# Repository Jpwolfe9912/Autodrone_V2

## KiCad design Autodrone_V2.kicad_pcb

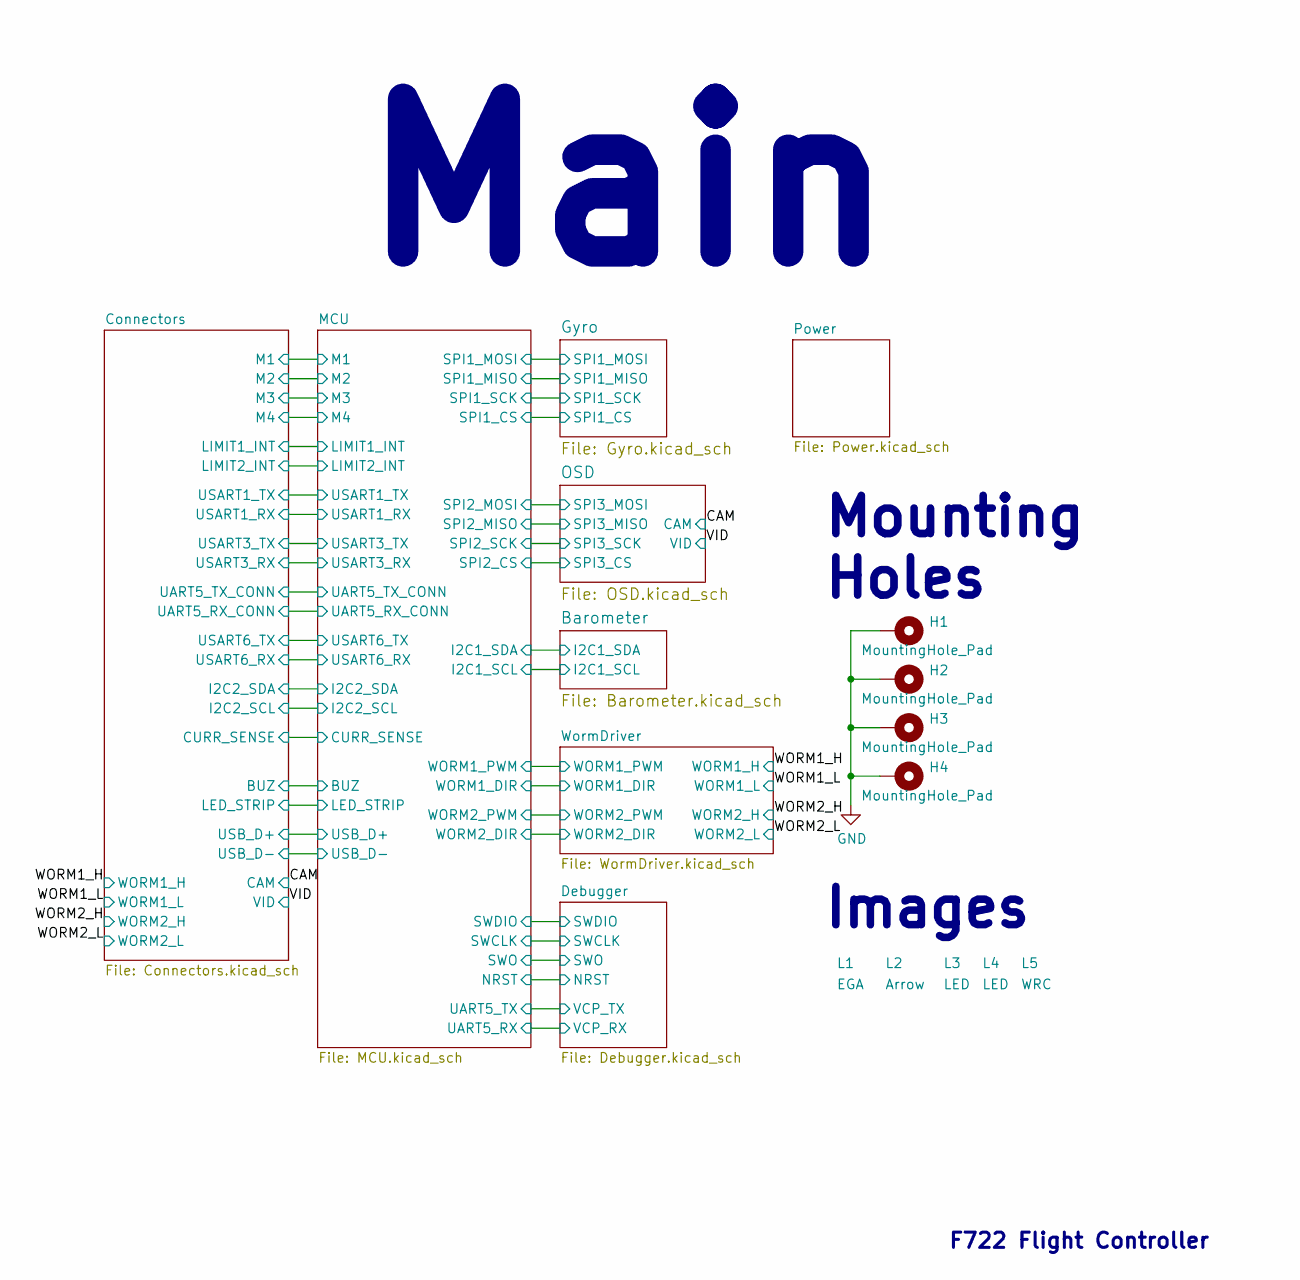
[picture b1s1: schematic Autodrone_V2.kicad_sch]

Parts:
H1, H2, H3, H4: MountingHole_Pad; MountingHole_6_4
L1: EGA
L2: Arrow
L3, L4: LED
L5: WRC; WRC2

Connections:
GND: H1.1, H2.1, H3.1, H4.1; also elsewhere on the board

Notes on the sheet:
Mounting Holes
Images
F722 Flight Controller
Main

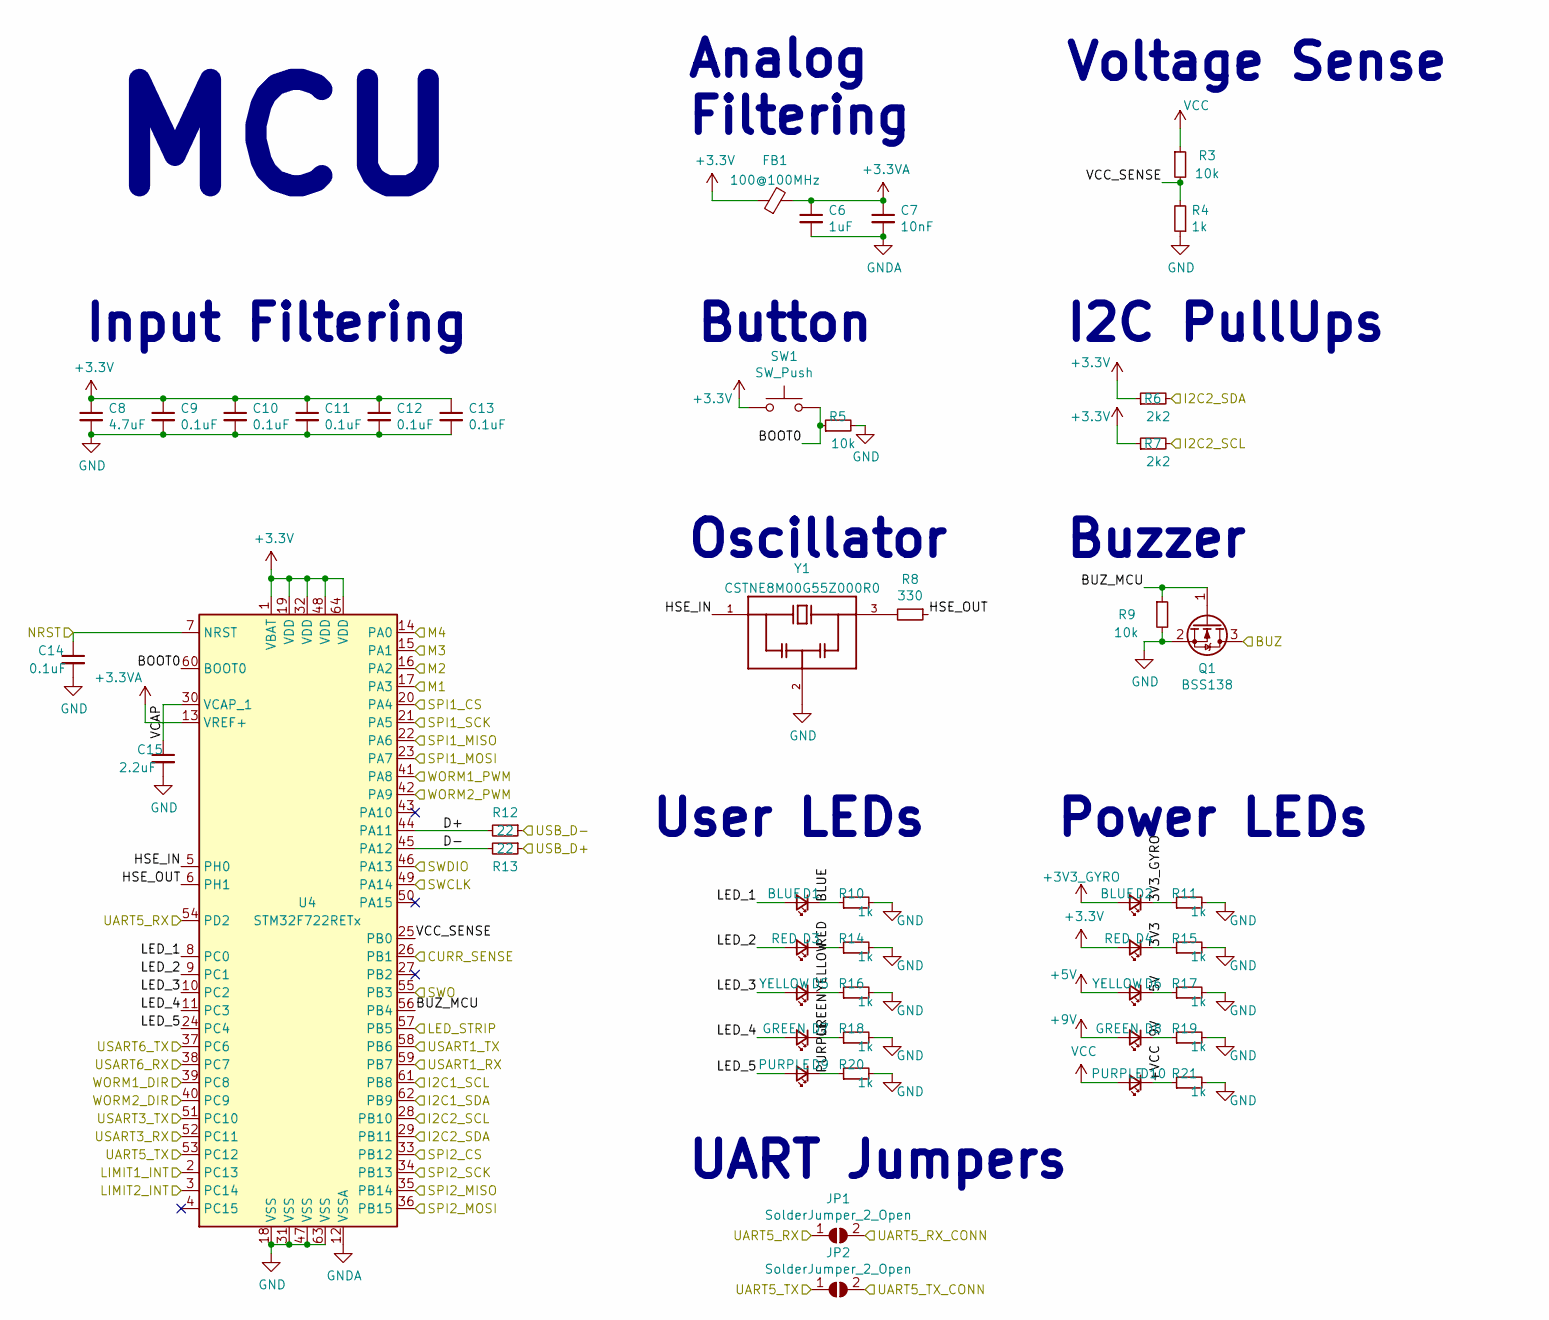
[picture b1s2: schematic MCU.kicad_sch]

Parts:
C6: 1uF; C_0402_1005Metric
C7: 10nF; C_0402_1005Metric
C8: 4.7uF; C_0402_1005Metric
C9, C10, C11, C12, C13, C14: 0.1uF; C_0402_1005Metric
C15: 2.2uF; C_0402_1005Metric
D1, D2: BLUE; LED_0603_1608Metric
D3, D4: RED; LED_0603_1608Metric
D5, D6: YELLOW; LED_0603_1608Metric
D7, D8: GREEN; LED_0603_1608Metric
D9, D10: PURPLE; LED_0603_1608Metric
FB1: 100@100MHz; L_0603_1608Metric
JP1, JP2: SolderJumper_2_Open; SolderJumper-2_P1.3mm_Open_TrianglePad1.0x1.5mm
Q1: BSS138; SOT-23
R3, R5, R9: 10k; R_0402_1005Metric
R4, R10, R11, R14, R15, R16, R17, R18, R19, R20, R21: 1k; R_0402_1005Metric
R6, R7: 2k2; R_0402_1005Metric
R8: 330; R_0402_1005Metric
R12, R13: 22; R_0402_1005Metric
SW1: SW_Push; SW_SPST_B3U-1000P
U4: STM32F722RETx; LQFP-64_10x10mm_P0.5mm
Y1: CSTNE8M00G55Z000R0; OSC_CSTNE8M00G55Z000R0; PARTREV JGC42-8858A

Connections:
+3.3VA: C6.1, C7.1, FB1.2, U4.13 (VREF+)
+3V3_GYRO: D2.2 (A); also elsewhere on the board
+5V: D6.2 (A); also elsewhere on the board
+9V: D8.2 (A); also elsewhere on the board
/Barometer/I2C1_SCL: U4.61 (PB8); also elsewhere on the board
/Barometer/I2C1_SDA: U4.62 (PB9); also elsewhere on the board
/Connectors/BUZ: Q1.3 (D); also elsewhere on the board
/Connectors/CURR_SENSE: U4.26 (PB1); also elsewhere on the board
/Connectors/I2C2_SCL: R7.2, U4.28 (PB10); also elsewhere on the board
/Connectors/I2C2_SDA: R6.2, U4.29 (PB11); also elsewhere on the board
/Connectors/LED_STRIP: U4.57 (PB5); also elsewhere on the board
/Connectors/LIMIT1_INT: U4.2 (PC13); also elsewhere on the board
/Connectors/LIMIT2_INT: U4.3 (PC14); also elsewhere on the board
/Connectors/M1: U4.17 (PA3); also elsewhere on the board
/Connectors/M2: U4.16 (PA2); also elsewhere on the board
/Connectors/M3: U4.15 (PA1); also elsewhere on the board
/Connectors/M4: U4.14 (PA0); also elsewhere on the board
/Connectors/UART5_RX_CONN: JP1.2 (B); also elsewhere on the board
/Connectors/UART5_TX_CONN: JP2.2 (B); also elsewhere on the board
/Connectors/USART1_RX: U4.59 (PB7); also elsewhere on the board
/Connectors/USART1_TX: U4.58 (PB6); also elsewhere on the board
/Connectors/USART3_RX: U4.52 (PC11); also elsewhere on the board
/Connectors/USART3_TX: U4.51 (PC10); also elsewhere on the board
/Connectors/USART6_RX: U4.38 (PC7); also elsewhere on the board
/Connectors/USART6_TX: U4.37 (PC6); also elsewhere on the board
/Connectors/USB_D+: R13.1; also elsewhere on the board
/Connectors/USB_D-: R12.1; also elsewhere on the board
/Debugger/NRST: C14.1, U4.7 (NRST); also elsewhere on the board
/Debugger/SWCLK: U4.49 (PA14); also elsewhere on the board
/Debugger/SWDIO: U4.46 (PA13); also elsewhere on the board
/Debugger/SWO: U4.55 (PB3); also elsewhere on the board
/Debugger/VCP_RX: JP1.1 (A), U4.54 (PD2); also elsewhere on the board
/Debugger/VCP_TX: JP2.1 (A), U4.53 (PC12); also elsewhere on the board
/Gyro/SPI1_CS: U4.20 (PA4); also elsewhere on the board
/Gyro/SPI1_MISO: U4.22 (PA6); also elsewhere on the board
/Gyro/SPI1_MOSI: U4.23 (PA7); also elsewhere on the board
/Gyro/SPI1_SCK: U4.21 (PA5); also elsewhere on the board
/MCU/3V3: D4.1 (K), R15.1
/MCU/3V3_GYRO: D2.1 (K), R11.1
/MCU/5V: D6.1 (K), R17.1
/MCU/9V: D8.1 (K), R19.1
/MCU/+VCC: D10.1 (K), R21.1
/MCU/BLUE: D1.1 (K), R10.1
/MCU/BOOT0: R5.1, SW1.2, U4.60 (BOOT0)
/MCU/BUZ_MCU: Q1.1 (G), R9.1, U4.56 (PB4)
/MCU/D+: R12.2, U4.44 (PA11)
/MCU/D-: R13.2, U4.45 (PA12)
/MCU/GREEN: D7.1 (K), R18.1
/MCU/HSE_IN: U4.5 (PH0), Y1.1
/MCU/HSE_OUT: R8.1, U4.6 (PH1)
/MCU/LED_1: D1.2 (A), U4.8 (PC0)
/MCU/LED_2: D3.2 (A), U4.9 (PC1)
/MCU/LED_3: D5.2 (A), U4.10 (PC2)
/MCU/LED_4: D7.2 (A), U4.11 (PC3)
/MCU/LED_5: D9.2 (A), U4.24 (PC4)
/MCU/PURPLE: D9.1 (K), R20.1
/MCU/RED: D3.1 (K), R14.1
/MCU/SPI2_CS: U4.33 (PB12); also elsewhere on the board
/MCU/SPI2_MISO: U4.35 (PB14); also elsewhere on the board
/MCU/SPI2_MOSI: U4.36 (PB15); also elsewhere on the board
/MCU/SPI2_SCK: U4.34 (PB13); also elsewhere on the board
/MCU/VCAP: C15.1, U4.30 (VCAP_1)
/MCU/VCC_SENSE: R3.2, R4.2, U4.25 (PB0)
/MCU/WORM1_DIR: U4.39 (PC8); also elsewhere on the board
/MCU/WORM1_PWM: U4.41 (PA8); also elsewhere on the board
/MCU/WORM2_DIR: U4.40 (PC9); also elsewhere on the board
/MCU/WORM2_PWM: U4.42 (PA9); also elsewhere on the board
/MCU/YELLOW: D5.1 (K), R16.1
GND: C8.2, C9.2, C10.2, C11.2, C12.2, C13.2, C14.2, C15.2, Q1.2 (S), R4.1, R5.2, R9.2, R10.2, R11.2, R14.2, R15.2, R16.2, R17.2, R18.2, R19.2, R20.2, R21.2, U4.18 (VSS), U4.31 (VSS), U4.47 (VSS), U4.63 (VSS), Y1.2; also elsewhere on the board
GNDA: C6.2, C7.2, U4.12 (VSSA)
unnamed: R8.2, Y1.3
VCC: D10.2 (A), R3.1; also elsewhere on the board

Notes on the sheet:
MCU
User LEDs
Buzzer
UART Jumpers
Analog Filtering
Input Filtering
Oscillator
I2C PullUps
Button
Voltage Sense
Power LEDs

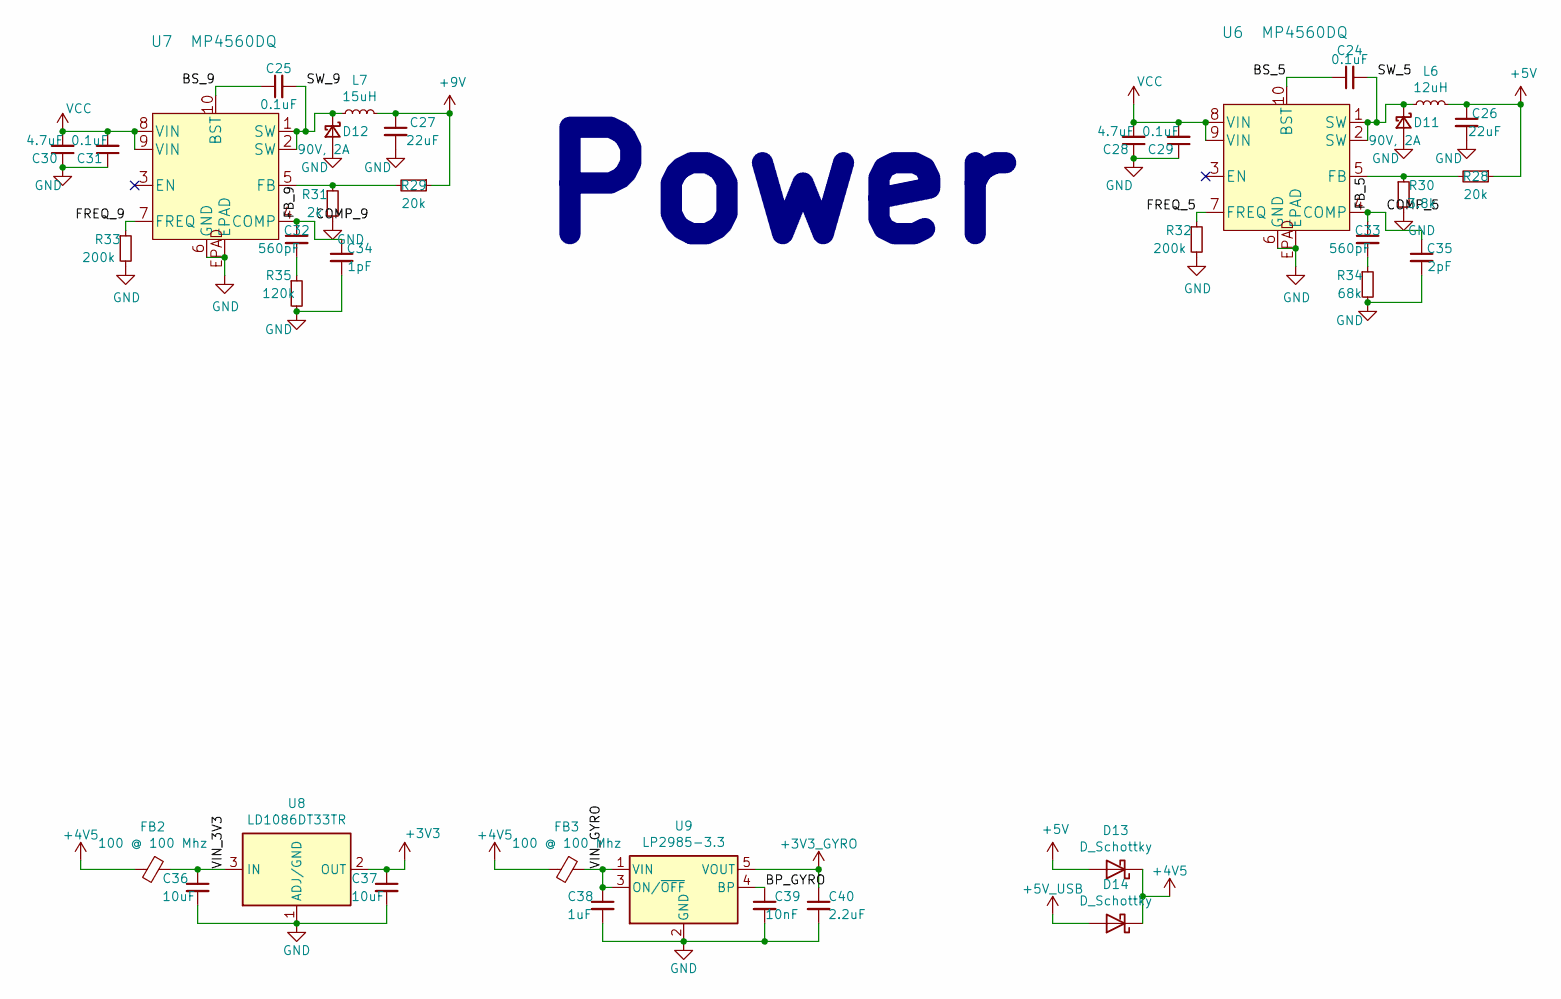
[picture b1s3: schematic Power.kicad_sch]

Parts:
C24, C25, C29, C31: 0.1uF; C_0402_1005Metric
C26, C27: 22uF; C_0805_2012Metric
C28, C30: 4.7uF; C_0402_1005Metric
C32, C33: 560pF; C_0402_1005Metric
C34: 1pF; C_0402_1005Metric
C35: 2pF; C_0402_1005Metric
C36, C37: 10uF; C_0402_1005Metric
C38: 1uF; C_0402_1005Metric
C39: 10nF; C_0402_1005Metric
C40: 2.2uF; C_0402_1005Metric
D11, D12: 90V, 2A; D_SOD-123F
D13, D14: D_Schottky; D_SOD-123F
FB2, FB3: 100 @ 100 Mhz; L_0603_1608Metric
L6: 12uH; L_Bourns_SRN3015
L7: 15uH; L_Bourns_SRN3015
R28, R29: 20k; R_0402_1005Metric
R30: 3.8k; R_0402_1005Metric
R31: 2k; R_0402_1005Metric
R32, R33: 200k; R_0402_1005Metric
R34: 68k; R_0402_1005Metric
R35: 120k; R_0402_1005Metric
U6, U7: MP4560DQ
U8: LD1086DT33TR; TO-252-2
U9: LP2985-3.3; SOT-23-5

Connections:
+3V3_GYRO: C40.1, U9.5 (VOUT); also elsewhere on the board
+4V5: D13.1 (K), D14.1 (K), FB2.2, FB3.2; also elsewhere on the board
+5V: C26.1, D13.2 (A), L6.2, R28.1; also elsewhere on the board
+5V_USB: D14.2 (A); also elsewhere on the board
+9V: C27.1, L7.2, R29.1; also elsewhere on the board
/Power/BP_GYRO: C39.1, U9.4 (BP)
/Power/BS_5: C24.1, U6.10 (BST)
/Power/BS_9: C25.1, U7.10 (BST)
/Power/COMP_5: C33.1, C35.1, U6.4 (COMP)
/Power/COMP_9: C32.1, C34.1, U7.4 (COMP)
/Power/FB_5: R28.2, R30.1, U6.5 (FB)
/Power/FB_9: R29.2, R31.1, U7.5 (FB)
/Power/FREQ_5: R32.1, U6.7 (FREQ)
/Power/FREQ_9: R33.1, U7.7 (FREQ)
/Power/SW_5: C24.2, D11.1 (K), L6.1, U6.1 (SW), U6.2 (SW)
/Power/SW_9: C25.2, D12.1 (K), L7.1, U7.1 (SW), U7.2 (SW)
/Power/VIN_3V3: C36.1, FB2.1, U8.3 (IN)
/Power/VIN_GYRO: C38.1, FB3.1, U9.1 (VIN), U9.3 (ON/~OFF)
GND: C26.2, C27.2, C28.1, C29.1, C30.1, C31.1, C34.2, C35.2, C36.2, C37.2, C38.2, C39.2, C40.2, D11.2 (A), D12.2 (A), R30.2, R31.2, R32.2, R33.2, R34.2, R35.2, U6.6 (GND), U6.EPAD, U7.6 (GND), U7.EPAD, U8.1 (ADJ/GND), U9.2 (GND); also elsewhere on the board
unnamed: C32.2, R35.1
unnamed: C33.2, R34.1
VCC: C28.2, C29.2, C30.2, C31.2, U6.8 (VIN), U6.9 (VIN), U7.8 (VIN), U7.9 (VIN); also elsewhere on the board

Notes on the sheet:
Power

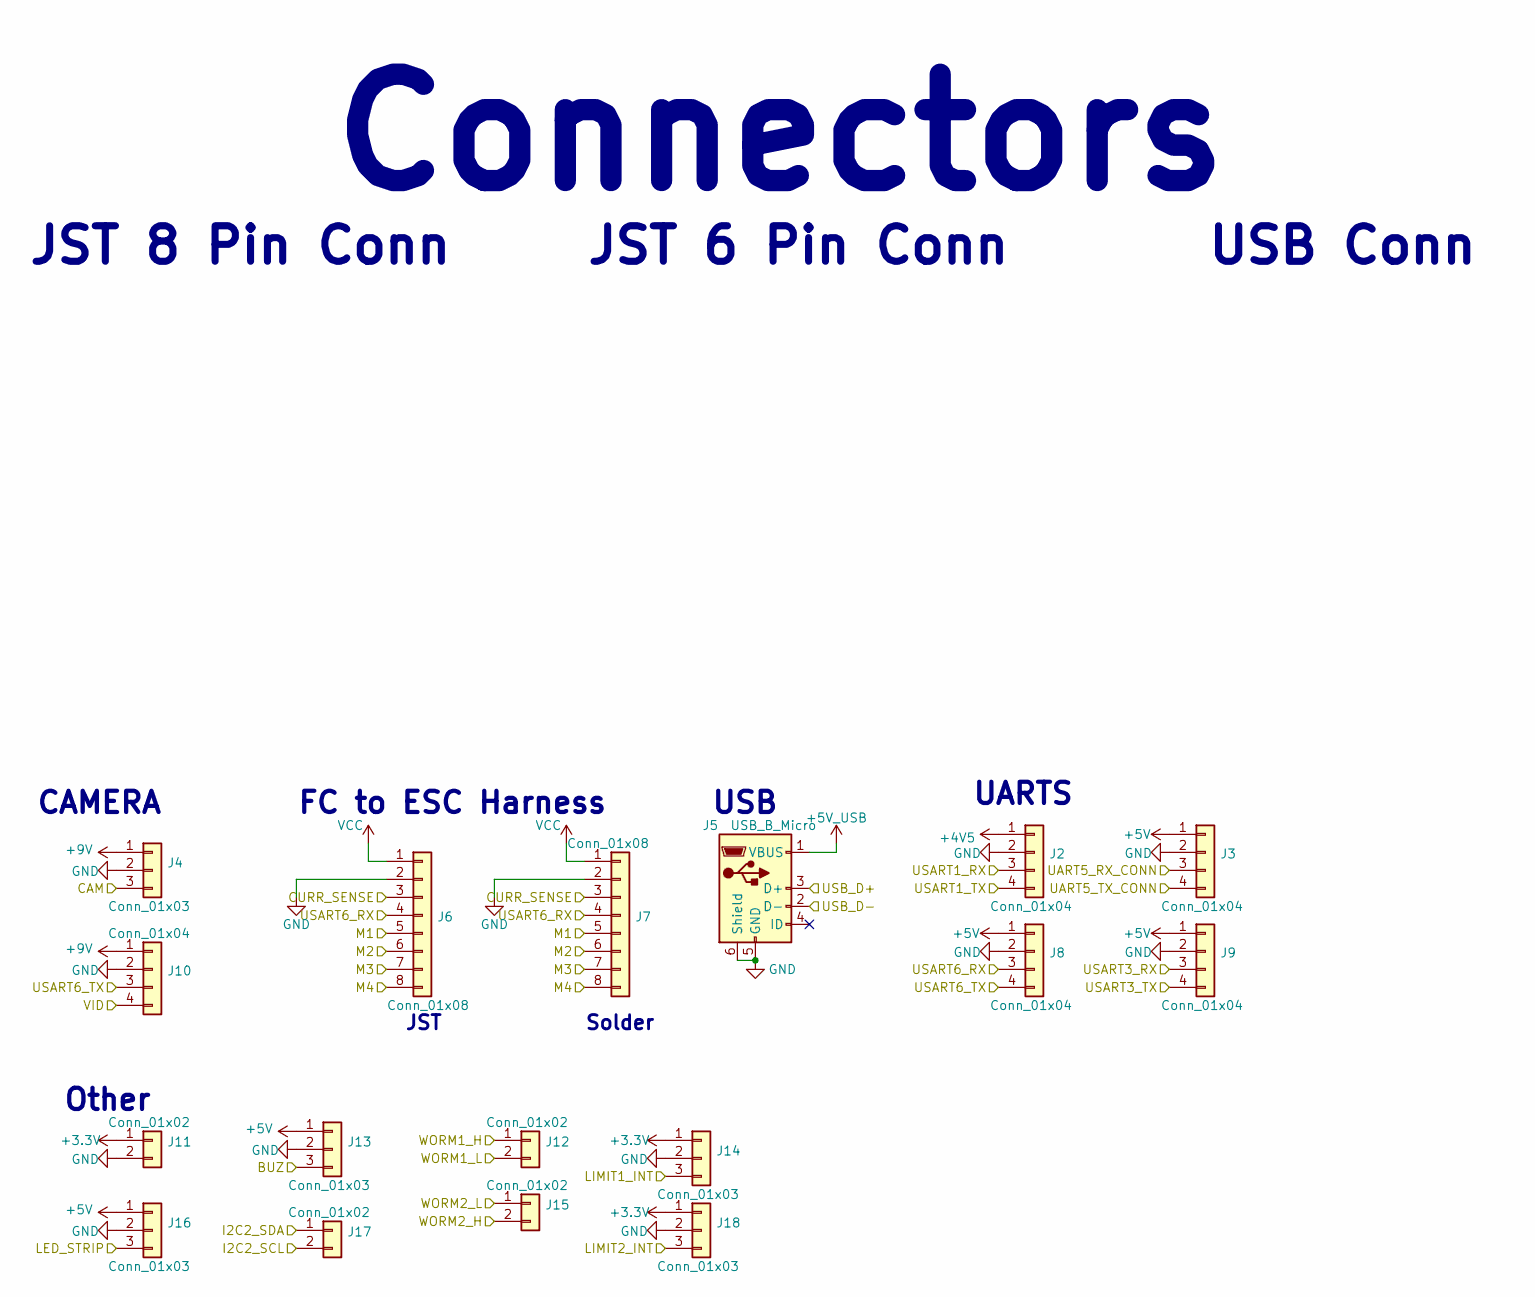
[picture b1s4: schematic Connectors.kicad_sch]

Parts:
J2, J3, J8, J9, J10: Conn_01x04; Conn_1x4
J4, J13, J14, J16, J18: Conn_01x03; Conn_1x3
J5: USB_B_Micro; USB_Micro-B_Amphenol_10103594-0001LF_Horizontal
J6: Conn_01x08; JST_SH_SM08B-SRSS-TB_1x08-1MP_P1.00mm_Horizontal
J7: Conn_01x08; Conn_8Edge
J11, J17: Conn_01x02; Conn_1x2
J12: Conn_01x02; Conn_Motor1
J15: Conn_01x02; Conn_Motor2

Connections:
+4V5: J2.1; also elsewhere on the board
+5V: J3.1, J8.1, J9.1, J13.1, J16.1; also elsewhere on the board
+5V_USB: J5.1 (VBUS); also elsewhere on the board
+9V: J4.1, J10.1; also elsewhere on the board
/CAM: J4.3; also elsewhere on the board
/Connectors/BUZ: J13.3; also elsewhere on the board
/Connectors/CURR_SENSE: J6.3, J7.3; also elsewhere on the board
/Connectors/I2C2_SCL: J17.2; also elsewhere on the board
/Connectors/I2C2_SDA: J17.1; also elsewhere on the board
/Connectors/LED_STRIP: J16.3; also elsewhere on the board
/Connectors/LIMIT1_INT: J14.3; also elsewhere on the board
/Connectors/LIMIT2_INT: J18.3; also elsewhere on the board
/Connectors/M1: J6.5, J7.5; also elsewhere on the board
/Connectors/M2: J6.6, J7.6; also elsewhere on the board
/Connectors/M3: J6.7, J7.7; also elsewhere on the board
/Connectors/M4: J6.8, J7.8; also elsewhere on the board
/Connectors/UART5_RX_CONN: J3.3; also elsewhere on the board
/Connectors/UART5_TX_CONN: J3.4; also elsewhere on the board
/Connectors/USART1_RX: J2.3; also elsewhere on the board
/Connectors/USART1_TX: J2.4; also elsewhere on the board
/Connectors/USART3_RX: J9.3; also elsewhere on the board
/Connectors/USART3_TX: J9.4; also elsewhere on the board
/Connectors/USART6_RX: J6.4, J7.4, J8.3; also elsewhere on the board
/Connectors/USART6_TX: J8.4, J10.3; also elsewhere on the board
/Connectors/USB_D+: J5.3 (D+); also elsewhere on the board
/Connectors/USB_D-: J5.2 (D-); also elsewhere on the board
/VID: J10.4; also elsewhere on the board
/WORM1_H: J12.1; also elsewhere on the board
/WORM1_L: J12.2; also elsewhere on the board
/WORM2_H: J15.2; also elsewhere on the board
/WORM2_L: J15.1; also elsewhere on the board
GND: J2.2, J3.2, J4.2, J5.5 (GND), J5.6 (Shield), J6.2, J7.2, J8.2, J9.2, J10.2, J11.2, J13.2, J14.2, J16.2, J18.2; also elsewhere on the board
VCC: J6.1, J7.1; also elsewhere on the board

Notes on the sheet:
USB
Solder
JST 8 Pin Conn
JST
CAMERA
UARTS
Connectors
FC to ESC Harness
Other
JST 6 Pin Conn
USB Conn

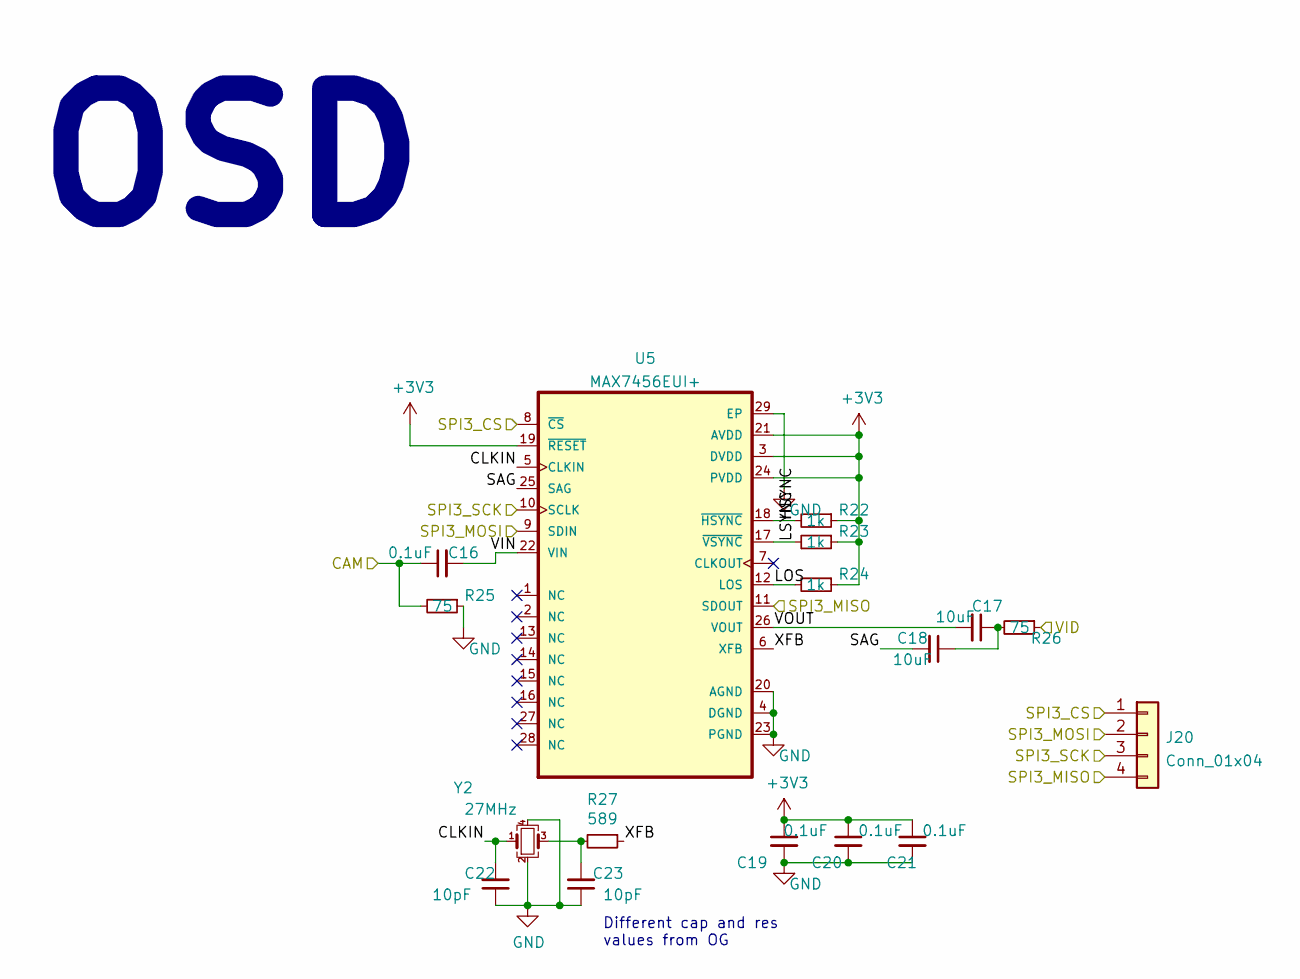
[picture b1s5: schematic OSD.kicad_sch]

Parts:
C16, C19, C20, C21: 0.1uF; C_0402_1005Metric
C17, C18: 10uF; C_0402_1005Metric
C22, C23: 10pF; C_0402_1005Metric
J20: Conn_01x04; SPI_Probe
R22, R23, R24: 1k; R_0402_1005Metric
R25, R26: 75; R_0402_1005Metric
R27: 589; R_0402_1005Metric
U5: MAX7456EUI+; MAX7456
Y2: 27MHz; Oscillator_SMD_Abracon_ASE-4Pin_3.2x2.5mm

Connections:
/CAM: C16.1, R25.2; also elsewhere on the board
/MCU/SPI2_CS: J20.1, U5.8 (~CS); also elsewhere on the board
/MCU/SPI2_MISO: J20.4, U5.11 (SDOUT); also elsewhere on the board
/MCU/SPI2_MOSI: J20.2, U5.9 (SDIN); also elsewhere on the board
/MCU/SPI2_SCK: J20.3, U5.10 (SCLK); also elsewhere on the board
/OSD/CLKIN: C22.2, U5.5 (CLKIN), Y2.1
/OSD/HSYNC: R22.2, U5.18 (~HSYNC)
/OSD/LOS: R24.2, U5.12 (LOS)
/OSD/LSYNC: R23.2, U5.17 (~VSYNC)
/OSD/SAG: C18.2, U5.25 (SAG)
/OSD/VIN: C16.2, U5.22 (VIN)
/OSD/VOUT: C17.2, U5.26 (VOUT)
/OSD/XFB: R27.1, U5.6 (XFB)
/VID: R26.1; also elsewhere on the board
GND: C19.2, C20.2, C21.2, C22.1, C23.1, R25.1, U5.4 (DGND), U5.20 (AGND), U5.23 (PGND), U5.29 (EP), Y2.2, Y2.4; also elsewhere on the board
unnamed: C17.1, C18.1, R26.2
unnamed: C23.2, R27.2, Y2.3

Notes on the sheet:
Different cap and res values from OG
OSD

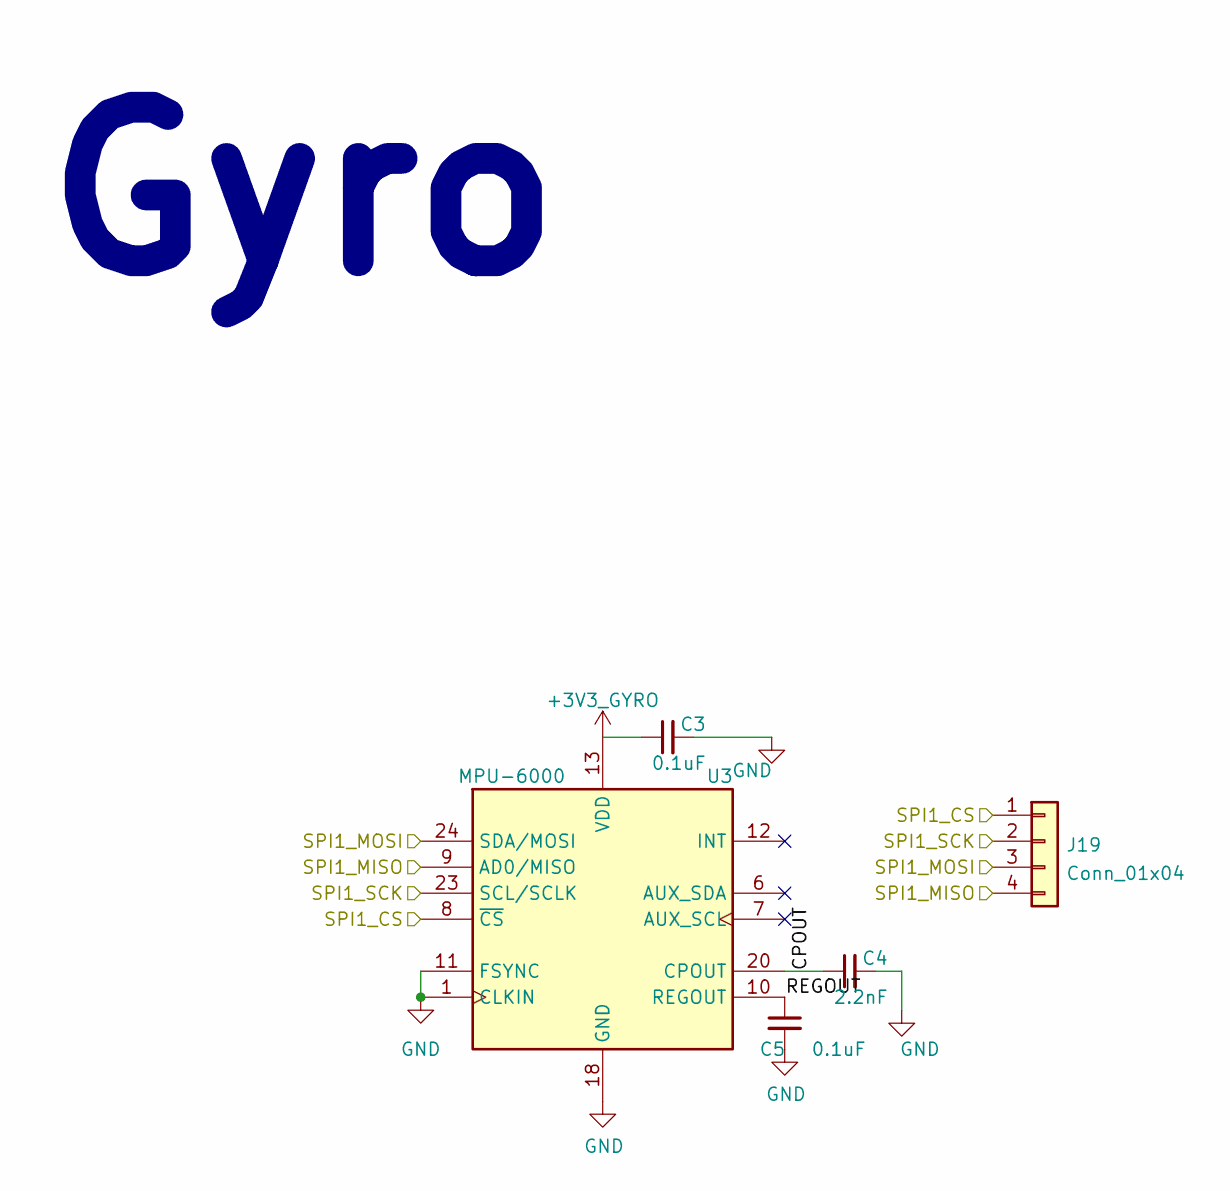
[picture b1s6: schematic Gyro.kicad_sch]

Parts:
C3, C5: 0.1uF; C_0402_1005Metric
C4: 2.2nF; C_0402_1005Metric
J19: Conn_01x04; SPI_Probe
U3: MPU-6000; InvenSense_QFN-24_4x4mm_P0.5mm

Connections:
+3V3_GYRO: C3.1, U3.13 (VDD); also elsewhere on the board
/Gyro/CPOUT: C4.1, U3.20 (CPOUT)
/Gyro/REGOUT: C5.1, U3.10 (REGOUT)
/Gyro/SPI1_CS: J19.1, U3.8 (~CS); also elsewhere on the board
/Gyro/SPI1_MISO: J19.4, U3.9 (AD0/MISO); also elsewhere on the board
/Gyro/SPI1_MOSI: J19.3, U3.24 (SDA/MOSI); also elsewhere on the board
/Gyro/SPI1_SCK: J19.2, U3.23 (SCL/SCLK); also elsewhere on the board
GND: C3.2, C4.2, C5.2, U3.1 (CLKIN), U3.11 (FSYNC), U3.18 (GND); also elsewhere on the board

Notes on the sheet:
Gyro

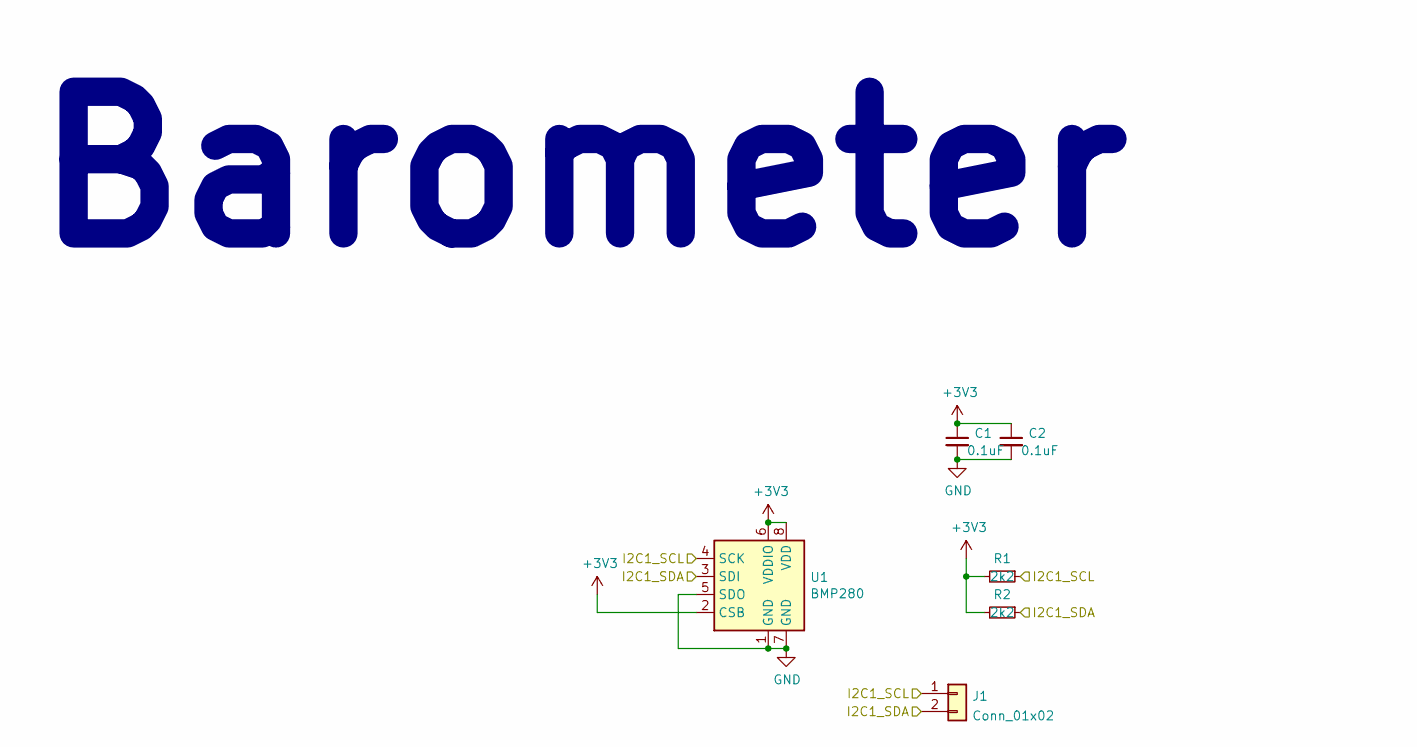
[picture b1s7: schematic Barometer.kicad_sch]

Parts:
C1, C2: 0.1uF; C_0402_1005Metric
J1: Conn_01x02; I2C_Probe
R1, R2: 2k2; R_0402_1005Metric
U1: BMP280; Bosch_LGA-8_2x2.5mm_P0.65mm_ClockwisePinNumbering

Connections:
/Barometer/I2C1_SCL: J1.1, R1.1, U1.4 (SCK); also elsewhere on the board
/Barometer/I2C1_SDA: J1.2, R2.1, U1.3 (SDI); also elsewhere on the board
GND: C1.2, C2.2, U1.1 (GND), U1.5 (SDO), U1.7 (GND); also elsewhere on the board

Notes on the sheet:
Barometer

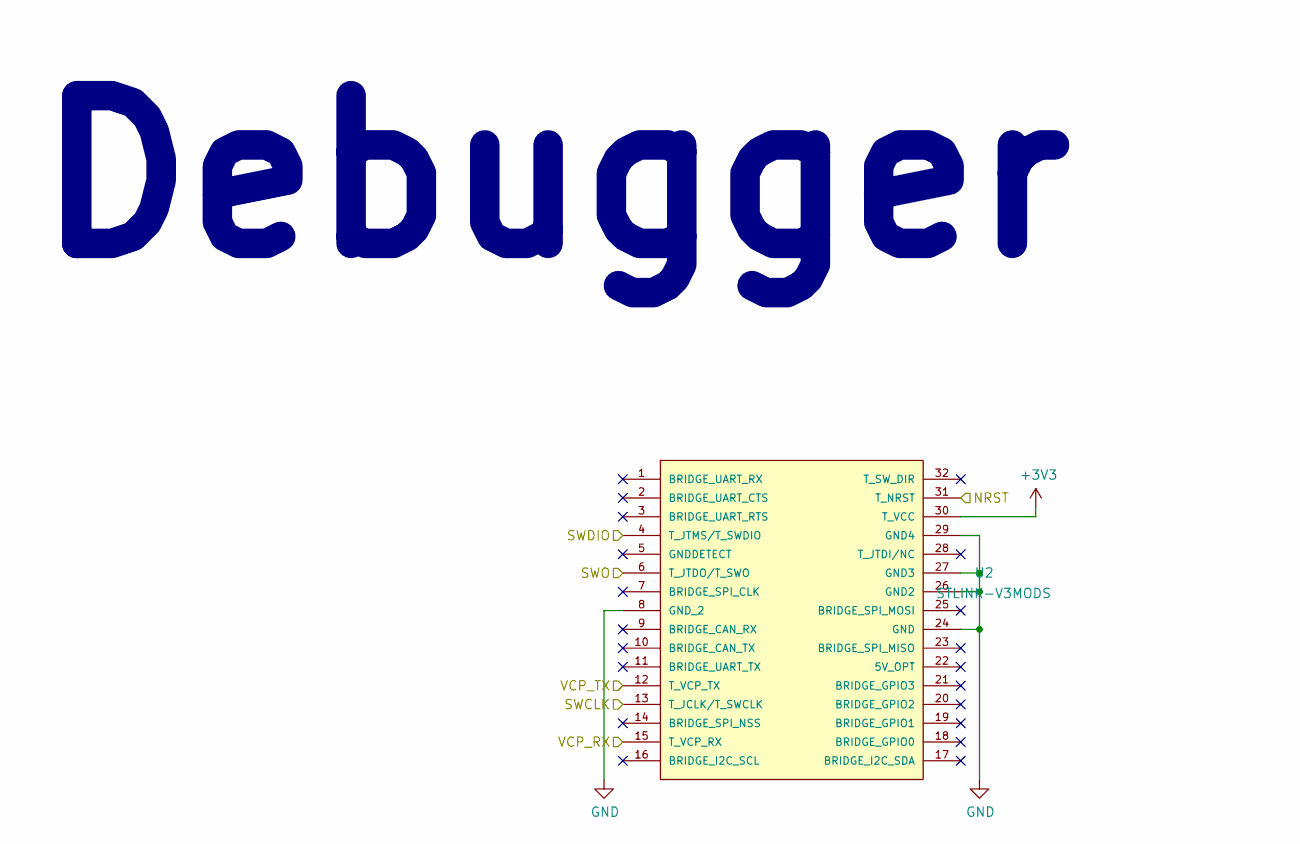
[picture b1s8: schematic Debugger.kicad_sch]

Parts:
U2: STLINK-V3MODS; STLINKV3MODS; MANUFACTURER_PART_NUMBER STLINKV3MOS

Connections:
/Debugger/NRST: U2.31 (T_NRST); also elsewhere on the board
/Debugger/SWCLK: U2.13 (T_JCLK/T_SWCLK); also elsewhere on the board
/Debugger/SWDIO: U2.4 (T_JTMS/T_SWDIO); also elsewhere on the board
/Debugger/SWO: U2.6 (T_JTDO/T_SWO); also elsewhere on the board
/Debugger/VCP_RX: U2.15 (T_VCP_RX); also elsewhere on the board
/Debugger/VCP_TX: U2.12 (T_VCP_TX); also elsewhere on the board
GND: U2.8 (GND_2), U2.24 (GND), U2.26 (GND2), U2.27 (GND3), U2.29 (GND4); also elsewhere on the board

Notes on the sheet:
Debugger

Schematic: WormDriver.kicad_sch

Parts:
C41: 10nF; C_0402_1005Metric
C42: 10uF; CP_EIA-1608-08_AVX-J
C43: 2.2uF; C_0402_1005Metric
J21: Conn_01x04; SPI_Probe
R36, R37: 47k; R_0402_1005Metric
U10: DRV8834RGER

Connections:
+5V: C41.2, C42.1, R36.2, R37.2, U10.15 (VM), U10.16 (VM); also elsewhere on the board
/MCU/WORM1_DIR: J21.1, U10.10 (APHASE); also elsewhere on the board
/MCU/WORM1_PWM: J21.4, U10.7 (AEN); also elsewhere on the board
/MCU/WORM2_DIR: J21.2, U10.9 (BPHASE); also elsewhere on the board
/MCU/WORM2_PWM: J21.3, U10.8 (BEN); also elsewhere on the board
/WORM1_H: U10.1 (AOUT1); also elsewhere on the board
/WORM1_L: U10.3 (AOUT2); also elsewhere on the board
/WORM2_H: U10.6 (BOUT1); also elsewhere on the board
/WORM2_L: U10.4 (BOUT2); also elsewhere on the board
/WormDriver/VCP: C41.1, U10.14 (VCP)
/WormDriver/VINT: C43.1, U10.17 (VINT)
/WormDriver/VREF: U10.19 (AVREF), U10.20 (BVREF), U10.21 (VREF0)
/WormDriver/nFAULT: R37.1, U10.13 (nFAULT)
/WormDriver/nSLEEP: R36.1, U10.22 (nSLEEP)
GND: C42.2, C43.2, U10.2 (AISEN), U10.5 (BISEN), U10.11 (M1), U10.12 (CONFIG), U10.18 (GND), U10.23 (BDECAY), U10.24 (ADECAY), U10.25 (EPAD); also elsewhere on the board

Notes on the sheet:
Worm Motor Driver

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
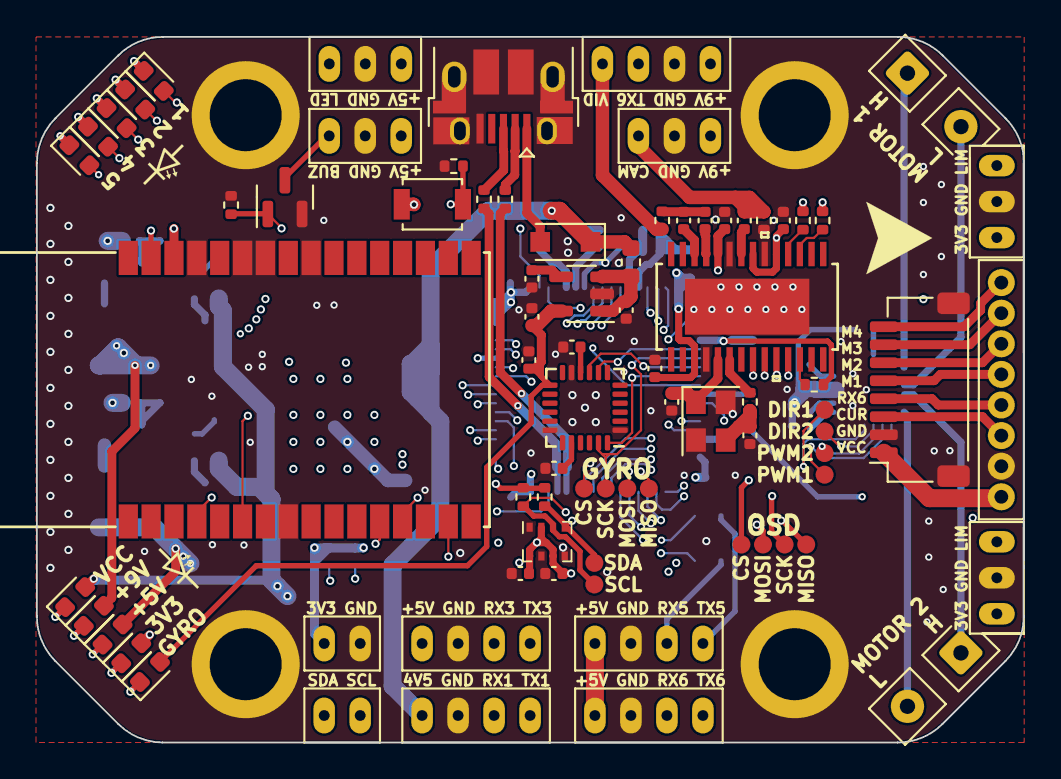
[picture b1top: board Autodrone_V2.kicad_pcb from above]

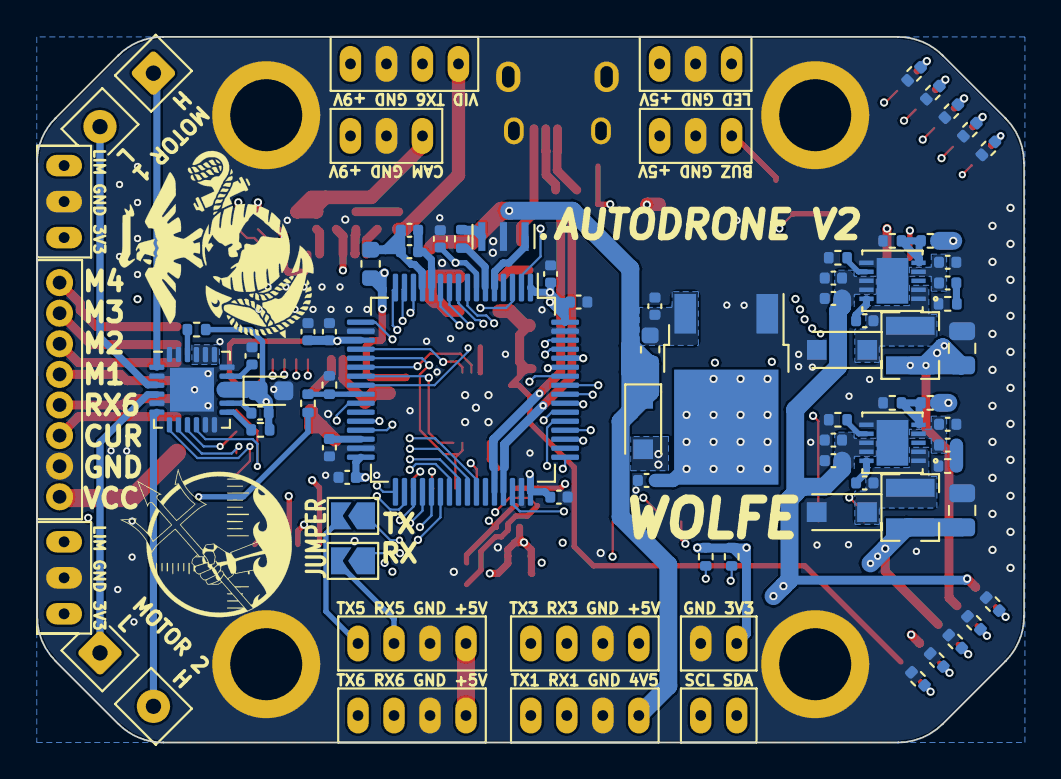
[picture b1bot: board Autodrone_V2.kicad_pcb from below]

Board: 6 copper layers, 54.8 x 39.2 mm, 145 parts (69 on the bottom side), 113 nets.

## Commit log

2022-01-02 Adding all new files
2022-01-02 Updated 3D Photos
2022-01-02 Updated PDF of schematic
2022-01-26 I guess I made some changes
2022-04-11 Added new files

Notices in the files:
parts and their libraries:
Copyright 2016 Accelerated Designs. All rights reserved.
Copyright 2021 Accelerated Designs. All rights reserved.
